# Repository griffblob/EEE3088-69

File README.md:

# EEE3088 Micromouse Project
## Group 69 
(Nice)
## Student Numbers:
TRCGRI001
SFRREN001

The project for our EEE3088F Electrcial Design course requires that we each design subsystems that will be integrated to build a Micro-mouse. This project covers the design and production of the sensing and power subsystems. Other systems such as processing subsystem, and motherboard are provided to us.

In this repository, one will find the detailed reports on how each subsystem was designed and tested and the gerber files for each subsystem.

Project files for the sensing subsystem can be found in: [Sensing](https://github.com/griffblob/EEE3088-69/tree/main/EEE3088%20Sensing)

Project files for the power subsystem can be found in: [Power](https://github.com/griffblob/EEE3088-69/tree/main/EEE3088%20Power)

Our reports can be found in [Reports](https://github.com/griffblob/EEE3088-69/tree/main/Reports). However, they will only be available after final submission closes to minimize the risk of plagarism.

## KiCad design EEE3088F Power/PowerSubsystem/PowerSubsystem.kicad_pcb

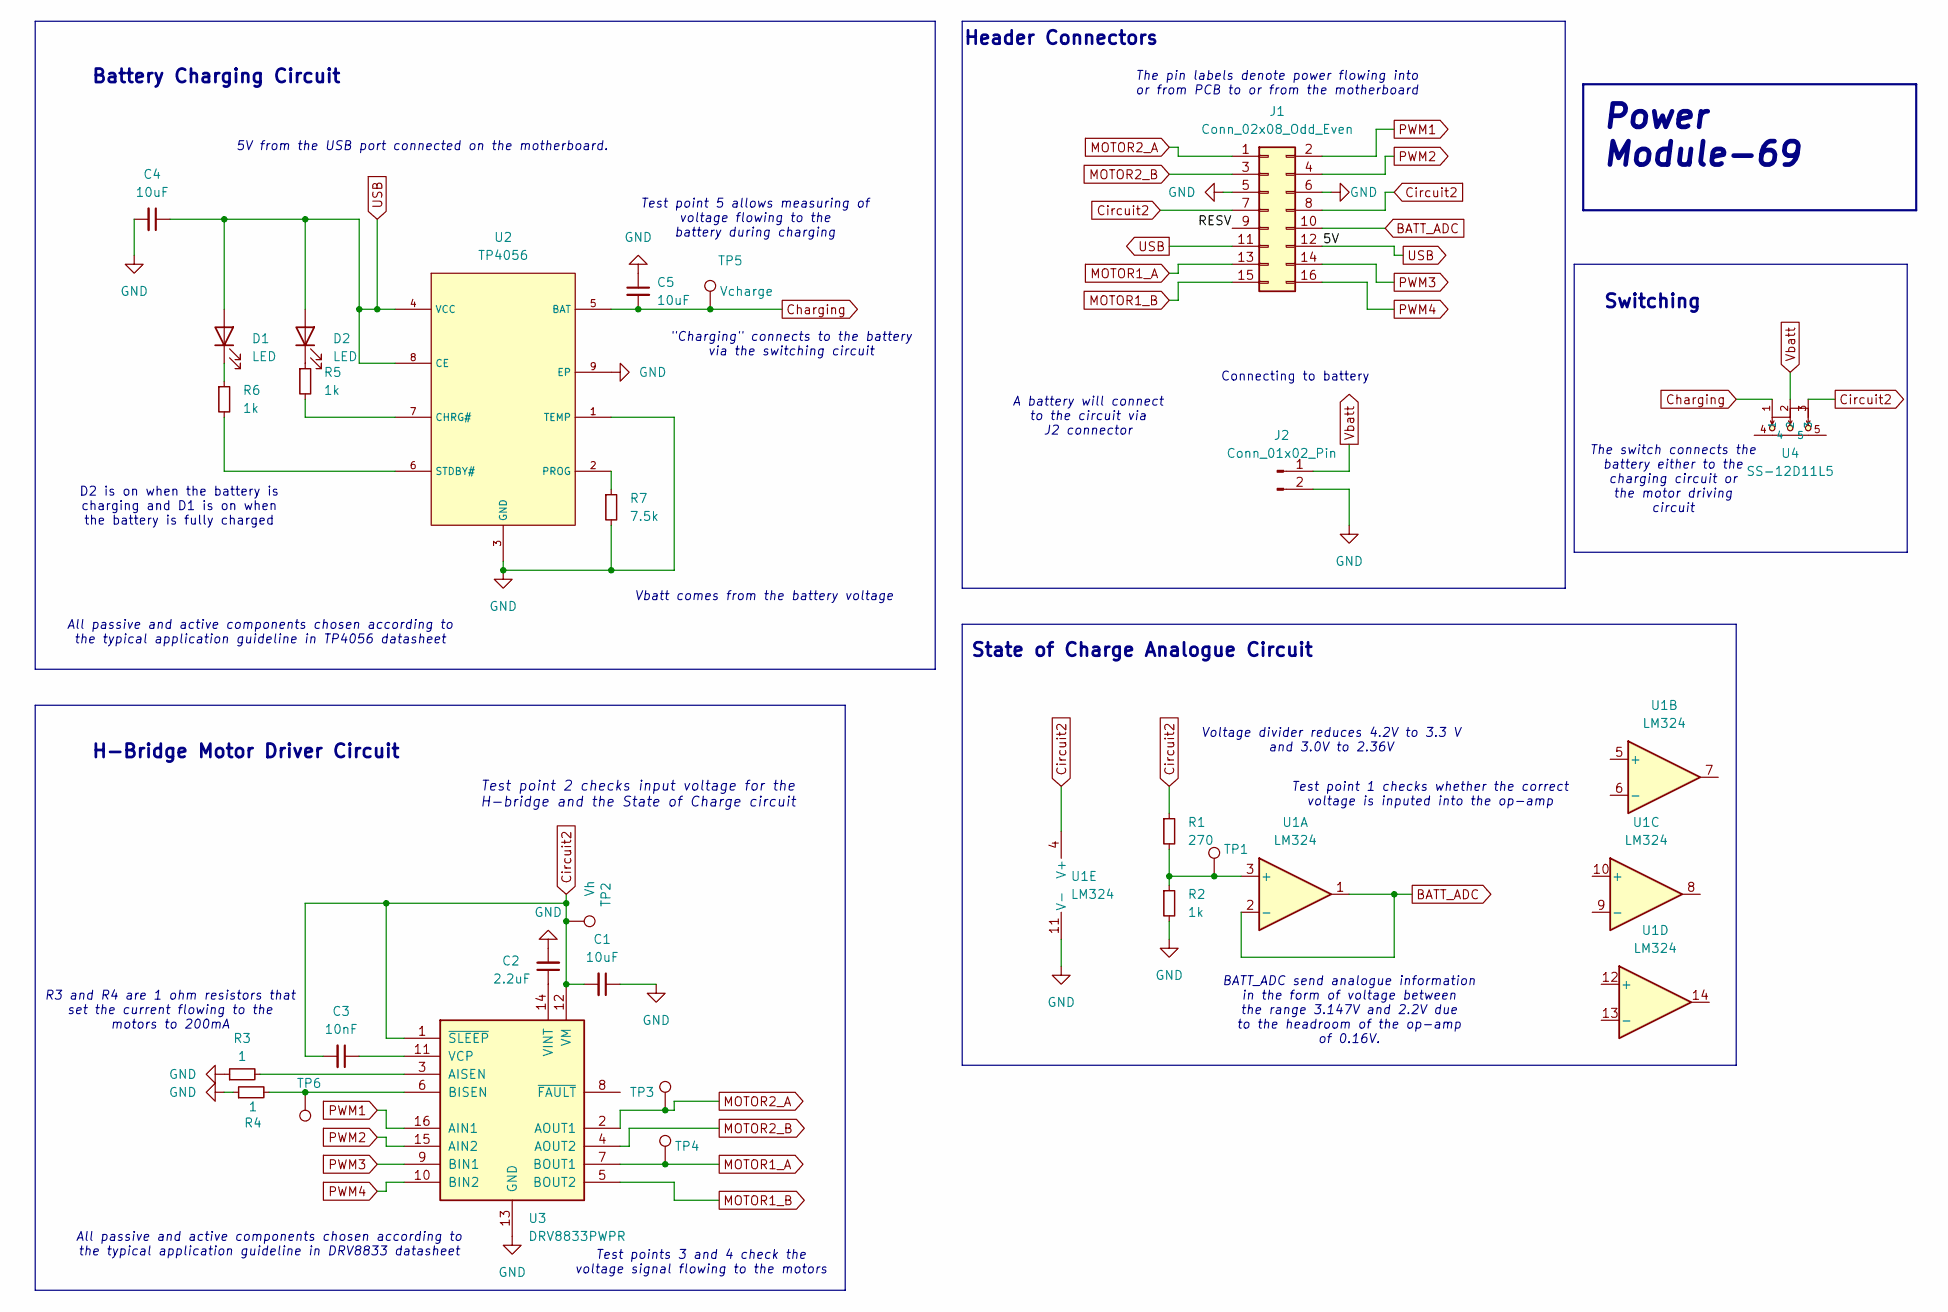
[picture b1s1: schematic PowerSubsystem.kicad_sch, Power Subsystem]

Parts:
C1, C4, C5: 10uF; C_0603_1608Metric; LCSC C19702
C2: 2.2uF; C_0603_1608Metric; LCSC C23630
C3: 10nF; C_0603_1608Metric; LCSC C57112
D1: LED; LED_0603_1608Metric; LCSC C2290
D2: LED; LED_0603_1608Metric; LCSC C2286
J1: Conn_02x08_Odd_Even; PinHeader_2x08_P2.54mm_Vertical
J2: Conn_01x02_Pin; JST_PH_B2B-PH-K_1x02_P2.00mm_Vertical
R1: 270; R_0603_1608Metric; LCSC C22966
R2, R5, R6: 1k; R_0603_1608Metric; LCSC C21190
R3, R4: 1; R_0603_1608Metric; LCSC C22936
R7: 7.5k; R_0603_1608Metric; LCSC C4211
TP1: Vadc; TestPoint_Pad_1.0x1.0mm
TP2: Vh; TestPoint_Pad_1.0x1.0mm
TP3: Vm1; TestPoint_Pad_1.0x1.0mm
TP4: Vm2; TestPoint_Pad_1.0x1.0mm
TP5: Vcharge; TestPoint_Pad_1.0x1.0mm
TP6: TestPoint; TestPoint_Pad_1.0x1.0mm
U1: LM324
U2: TP4056; ESOP-8_L4.9-W3.9-P1.27-LS6.0-BL-EP; LCSC C16581
U3: DRV8833PWPR; TSSOP-16-1EP_4.4x5mm_P0.65mm; LCSC C50506
U4: SS-12D11L5; SW-TH_SS-12D11L5; LCSC C319010

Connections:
/RESV: J1.9
BATT_ADC: J1.10, U1.1, U1.2 (-)
Charging: C5.2, TP5.1, U2.5 (BAT), U4.1
Circuit2: C1.2, C3.2, J1.7, J1.8, R1.1, TP2.1, U1.4 (V+), U3.1 (~SLEEP), U3.12 (VM), U4.3
GND: C1.1, C2.2, C4.2, C5.1, J1.5, J1.6, J2.2, R2.2, R3.1, R4.1, R7.2, U1.11 (V-), U2.1 (TEMP), U2.3 (GND), U2.9 (EP), U3.13 (GND), U3.17 (GND)
MOTOR1_A: J1.13, TP4.1, U3.7 (BOUT1)
MOTOR1_B: J1.15, U3.5 (BOUT2)
MOTOR2_A: J1.1, TP3.1, U3.2 (AOUT1)
MOTOR2_B: J1.3, U3.4 (AOUT2)
unnamed: D1.1 (K), R6.1
unnamed: D2.1 (K), R5.1
unnamed: R1.2, R2.1, TP1.1, U1.3 (+)
unnamed: R5.2, U2.7 (CHRG#)
unnamed: R7.1, U2.2 (PROG)
unnamed: R6.2, U2.6 (STDBY#)
unnamed: R3.2, U3.3 (AISEN)
unnamed: R4.2, TP6.1, U3.6 (BISEN)
unnamed: C3.1, U3.11 (VCP)
unnamed: C2.1, U3.14 (VINT)
PWM1: J1.2, U3.16 (AIN1)
PWM2: J1.4, U3.15 (AIN2)
PWM3: J1.14, U3.9 (BIN1)
PWM4: J1.16, U3.10 (BIN2)
USB: C4.1, D1.2 (A), D2.2 (A), J1.11, J1.12, U2.4 (VCC), U2.8 (CE)
Vbatt: J2.1, U4.2

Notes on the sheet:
Battery Charging Circuit
H-Bridge Motor Driver Circuit
Power Module-69
Switching
BATT_ADC send analogue information in the form of voltage between the range 3.147V and 2.2V due to the headroom of the op-amp of 0.16V.
Test point 1 checks whether the correct voltage is inputed into the op-amp
All passive and active components chosen according to the typical application guideline in DRV8833 datasheet
The switch connects the battery either to the charging circuit or the motor driving circuit
Test point 2 checks input voltage for the H-bridge and the State of Charge circuit
All passive and active components chosen according to the typical application guideline in TP4056 datasheet
Connecting to battery
5V from the USB port connected on the motherboard.
Test points 3 and 4 check the voltage signal flowing to the motors
Header Connectors
Voltage divider reduces 4.2V to 3.3 V and 3.0V to 2.36V
"Charging" connects to the battery via the switching circuit
A battery will connect to the circuit via J2 connector
D2 is on when the battery is charging and D1 is on when the battery is fully charged
R3 and R4 are 1 ohm resistors that set the current flowing to the motors to 200mA
Test point 5 allows measuring of voltage flowing to the battery during charging
State of Charge Analogue Circuit
Vbatt comes from the battery voltage
The pin labels denote power flowing into or from PCB to or from the motherboard

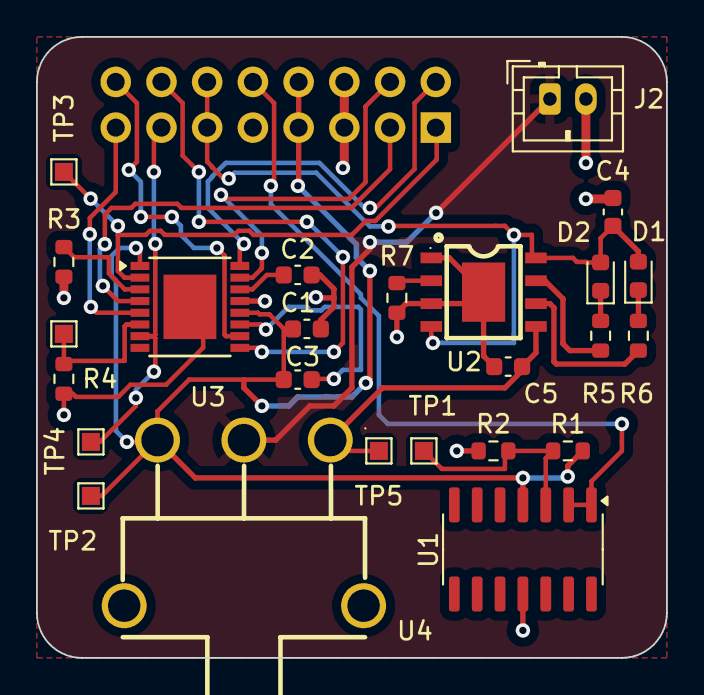
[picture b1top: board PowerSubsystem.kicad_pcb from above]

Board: 2 copper layers, 35.0 x 34.5 mm, 26 parts (1 on the bottom side), 24 nets.

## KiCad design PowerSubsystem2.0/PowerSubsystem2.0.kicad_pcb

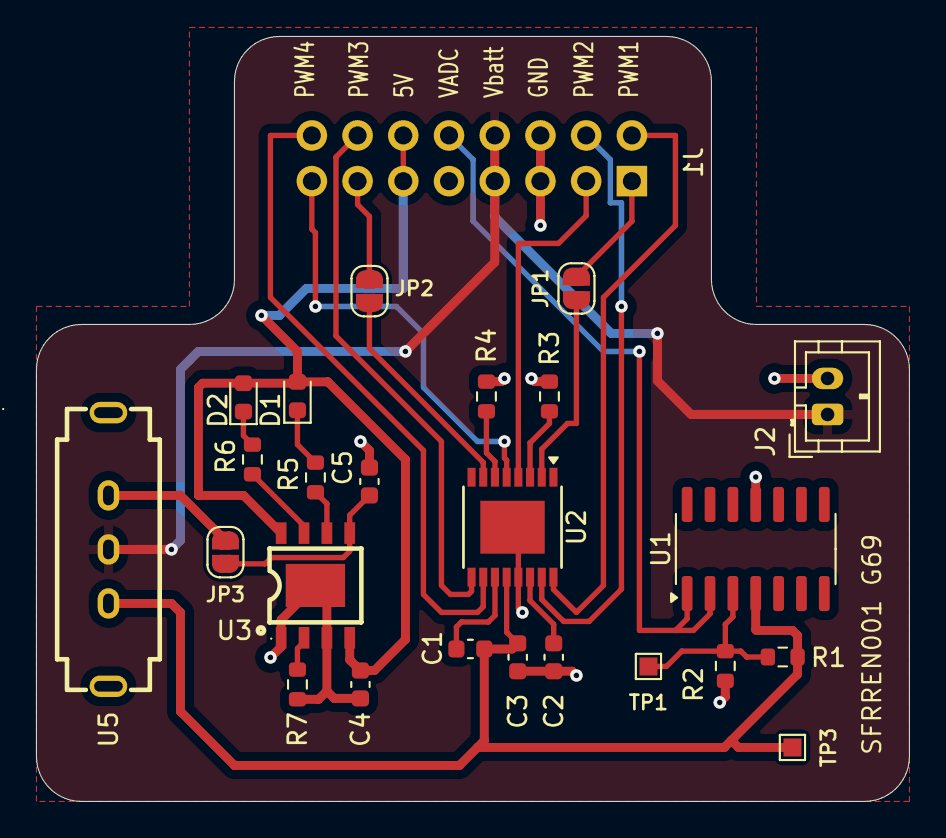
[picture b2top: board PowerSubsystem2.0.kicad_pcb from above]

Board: 2 copper layers, 48.5 x 42.5 mm, 25 parts (1 on the bottom side), 27 nets.

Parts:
C1: 10nF; C_0603_1608Metric
C2: 2.2uF; C_0603_1608Metric
C3, C4, C5: 10uF; C_0603_1608Metric
D1, D2: LED; LED_0603_1608Metric
J1: Conn_02x08_Odd_Even; PinHeader_2x08_P2.54mm_Vertical
J2: Conn_01x02_Pin; JST_PH_B2B-PH-K_1x02_P2.00mm_Vertical
JP1, JP2, JP3: SolderJumper_2_Open; SolderJumper-2_P1.3mm_Open_RoundedPad1.0x1.5mm
R1: 270; R_0603_1608Metric
R2, R5, R6: 1k; R_0603_1608Metric
R3, R4: 1; R_0603_1608Metric
R7: 7.5k; R_0603_1608Metric
TP1: Vadc; TestPoint_Pad_1.0x1.0mm
TP3: Vh; TestPoint_Pad_1.0x1.0mm
U1: LM324; SOIC-14_3.9x8.7mm_P1.27mm
U2: DRV8833PWPR; TSSOP-16-1EP_4.4x5mm_P0.65mm
U3: TP4056; ESOP-8_L4.9-W3.9-P1.27-LS6.0-BL-EP
U5: SK-12F02-G030; SW-TH_G-SWITCH_SK-12F02-G030

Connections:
/Motor1_A: J1.13, JP2.2 (B)
/Motor1_B: J1.15, U2.5 (BOUT2)
/Motor2_A: J1.1, JP1.2 (B)
/Motor2_B: J1.3, U2.4 (AOUT2)
/PWM1: J1.2, U2.16 (AIN1)
/PWM2: J1.4, U2.15 (AIN2)
/PWM3: J1.14, U2.9 (BIN1)
/PWM4: J1.16, U2.10 (BIN2)
/Vbatt: J1.7, J1.8, J2.1, U5.2
/Vusb: C4.1, D1.2 (A), D2.2 (A), J1.11, J1.12, U3.4 (VCC), U3.8 (CE)
Charging: JP3.2 (B), U5.1
GND: C2.2, C3.1, C4.2, C5.1, J1.5, J1.6, J2.2, R2.2, R3.1, R4.1, R7.2, U1.11 (V-), U2.13 (GND), U2.17 (GND), U3.1 (TEMP), U3.3 (GND), U3.9 (EP)
H-bridge: C1.2, C3.2, R1.1, TP3.1, U1.4 (V+), U2.12 (VM), U5.3
unnamed: D1.1 (K), R5.1
unnamed: D2.1 (K), R6.1
unnamed: JP1.1 (A), U2.2 (AOUT1)
unnamed: JP2.1 (A), U2.7 (BOUT1)
unnamed: C5.2, JP3.1 (A), U3.5 (BAT)
unnamed: R1.2, R2.1, TP1.1, U1.3 (+)
unnamed: R3.2, U2.3 (AISEN)
unnamed: R4.2, U2.6 (BISEN)
unnamed: C1.1, U2.11 (VCP)
unnamed: C2.1, U2.14 (VINT)
unnamed: R6.2, U3.7 (CHRG#)
unnamed: R7.1, U3.2 (PROG)
unnamed: R5.2, U3.6 (STDBY#)
VADC: J1.10, U1.1, U1.2 (-)

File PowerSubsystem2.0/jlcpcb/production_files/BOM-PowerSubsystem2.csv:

Comment,Designator,Footprint,LCSC
TP4056,U3,ESOP-8_L4.9-W3.9-P1.27-LS6.0-BL-EP,C16581
1k,"R2,R5,R6",R_0603_1608Metric,C21190
LED,D2,LED_0603_1608Metric,C2286
LED,D1,LED_0603_1608Metric,C2290
1,"R3,R4",R_0603_1608Metric,C22936
270,R1,R_0603_1608Metric,C22966
7.5k,R7,R_0603_1608Metric,C23234
2.2uF,C2,C_0603_1608Metric,C23630
SK-12F02-G030,U5,SW-TH_G-SWITCH_SK-12F02-G030,C2848892
DRV8833PWPR,U2,TSSOP-16-1EP_4.4x5mm_P0.65mm,C50506
10nF,C1,C_0603_1608Metric,C57112
LM324,U1,SOIC-14_3.9x8.7mm_P1.27mm,C71035
10uF,"C3,C4,C5",C_0603_1608Metric,C96446

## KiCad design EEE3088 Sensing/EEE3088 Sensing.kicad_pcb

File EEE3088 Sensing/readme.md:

# Sensing Subsystem
This subsystem was designed by TRCGRI001 and is they eyes of our robot

Here you will find the KICAD project files. 

🍑

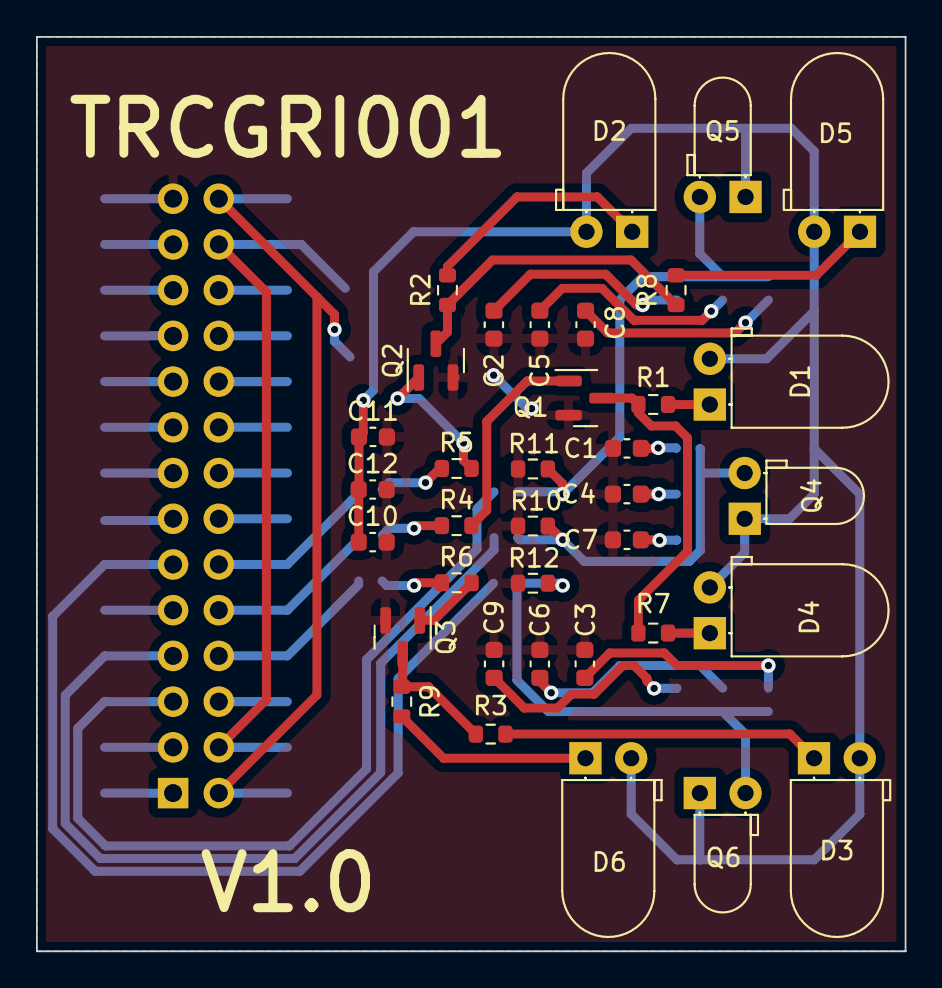
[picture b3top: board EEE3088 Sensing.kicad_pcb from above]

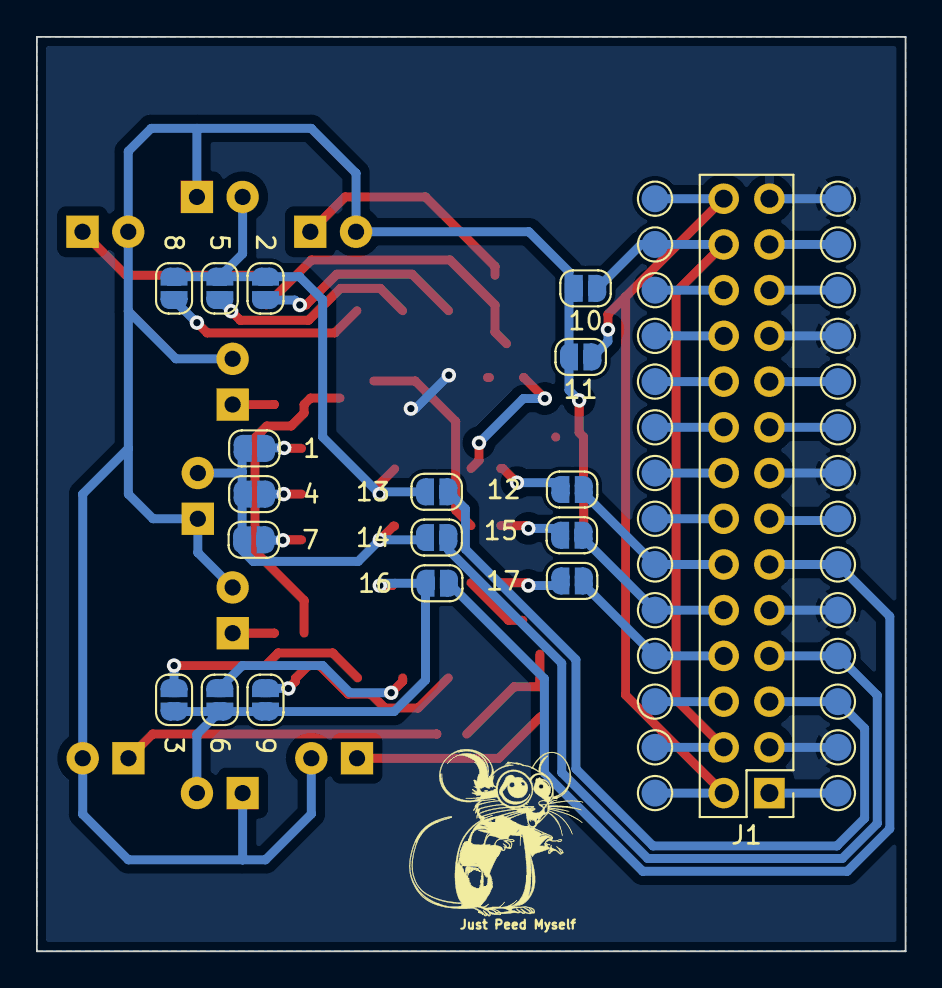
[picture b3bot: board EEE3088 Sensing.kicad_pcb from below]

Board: 2 copper layers, 48.3 x 50.8 mm, 82 parts (46 on the bottom side), 50 nets.

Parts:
1, 2, 3, 4, 5, 6, 7, 8, 9, 10, 11, 12, 13, 14, 15, 16, 17: SolderJumper_2_Open; SolderJumper-2_P1.3mm_Open_RoundedPad1.0x1.5mm
C1, C2, C3, C10: 100n CC0603KRX7R9BB104; C_0603_1608Metric
C4, C5, C6: 10n 0603B103K500NT; C_0603_1608Metric
C7, C8, C9: 1n CL10B102KB8NNNC; C_0603_1608Metric
C11: 2.2u CL10A225KO8NNNC; C_0603_1608Metric
C12: 10u CL10A106MA8NRNC; C_0603_1608Metric
D1, D2, D3, D4, D5, D6: SFH 4544; LED_D5.0mm_Horizontal_O1.27mm_Z3.0mm_IRBlack
J1: Conn_02x14_Odd_Even; PinHeader_2x14_P2.54mm_Vertical
Q1, Q2, Q3: BC847; SOT-23
Q4, Q5, Q6: TEFT4300; LED_D3.0mm_Horizontal_O1.27mm_Z2.0mm_IRBlack
R1, R2, R3, R7, R8, R9: 10; R_0603_1608Metric
R4, R5, R6: 620; R_0603_1608Metric
R10, R11, R12: 1.8K; R_0603_1608Metric
TP1, TP2, TP3, TP4, TP5, TP6, TP7, TP8, TP9, TP10, TP11, TP12, TP13, TP14, TP15, TP16, TP17, TP18, TP19, TP20, TP21, TP22, TP23, TP24, TP25, TP26, TP27, TP28: TestPoint; TestPoint_Pad_D1.5mm

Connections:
3V3: 11.1 (A), J1.2, J1.28, TP15.1, TP28.1
AB0: J1.25, TP13.1
BATT: 10.1 (A), J1.4, J1.26, TP16.1, TP27.1
GND: C1.2, C2.2, C3.2, C4.2, C5.2, C6.2, C7.2, C8.2, C9.2, C10.2, C11.2, C12.2, J1.3, J1.9, J1.15, J1.21, J1.27, Q1.2 (E), Q2.2 (E), Q3.2 (E), R10.2, R11.2, R12.2, TP2.1, TP5.1, TP8.1, TP11.1, TP14.1
unnamed: 1.1 (A), C1.1
unnamed: 2.1 (A), C2.1
unnamed: 3.1 (A), C3.1
unnamed: 4.1 (A), C4.1
unnamed: 5.1 (A), C5.1
unnamed: 6.1 (A), C6.1
unnamed: 7.1 (A), C7.1
unnamed: 8.1 (A), C8.1
unnamed: 9.1 (A), C9.1
unnamed: D1.1 (K), R1.1
unnamed: D2.1 (K), R2.1
unnamed: D3.1 (K), R3.1
unnamed: D4.1 (K), R7.1
unnamed: D5.1 (K), R8.1
unnamed: D6.1 (K), R9.1
unnamed: Q1.1 (B), R4.2
unnamed: Q1.3 (C), R1.2, R7.2
unnamed: Q2.1 (B), R5.2
unnamed: Q2.3 (C), R2.2, R8.2
unnamed: Q3.1 (B), R6.2
unnamed: Q3.3 (C), R3.2, R9.2
PA3: 13.1 (A), J1.5, TP3.1
PA4: 14.1 (A), J1.7, TP4.1
PA5: 16.1 (A), J1.11, TP6.1
PA6: J1.13, TP7.1
PA7: J1.17, TP9.1
PC4: J1.19, TP10.1
PC5: J1.23, TP12.1
PE8: J1.22, TP25.1
PE9: J1.20, TP24.1
PE10: J1.18, TP23.1
PE11: J1.16, TP22.1
PE12: J1.14, TP21.1
PE13: 12.1 (A), J1.12, TP20.1
PE14: 15.1 (A), J1.10, TP19.1
PE15: 17.1 (A), J1.8, TP18.1
RESV1: J1.24, TP26.1
RESV2: J1.6, TP17.1
RESV3: J1.1, TP1.1
VinL: 12.2 (B), R5.1
VinM: 15.2 (B), R4.1
VinR: 17.2 (B), R6.1
VoutL: 2.2 (B), 5.2 (B), 8.2 (B), 13.2 (B), Q5.2 (E), R11.1
VoutM: 1.2 (B), 4.2 (B), 7.2 (B), 14.2 (B), Q4.2 (E), R10.1
VoutR: 3.2 (B), 6.2 (B), 9.2 (B), 16.2 (B), Q6.2 (E), R12.1
vcc: 10.2 (B), 11.2 (B), C10.1, C11.1, C12.1, D1.2 (A), D2.2 (A), D3.2 (A), D4.2 (A), D5.2 (A), D6.2 (A), Q4.1 (C), Q5.1 (C), Q6.1 (C)

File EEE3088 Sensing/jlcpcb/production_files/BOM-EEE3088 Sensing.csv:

Comment,Designator,Footprint,LCSC
TEFT4300,"Q4,Q5,Q6",LED_D3.0mm_Horizontal_O1.27mm_Z2.0mm_IRBlack,C118301
100n CC0603KRX7R9BB104,"C1,C10,C2,C3",C_0603_1608Metric,C14663
1n CL10B102KB8NNNC,"C7,C8,C9",C_0603_1608Metric,C1588
10,"R1,R2,R3,R7,R8,R9",R_0603_1608Metric,C22859
620,"R4,R5,R6",R_0603_1608Metric,C23220
2.2u CL10A225KO8NNNC,C11,C_0603_1608Metric,C23630
 SFH 4544,"D1,D2,D3,D4,D5,D6",LED_D5.0mm_Horizontal_O1.27mm_Z3.0mm_IRBlack,C2900370
1.8K,"R10,R11,R12",R_0603_1608Metric,C4177
10n 0603B103K500NT,"C4,C5,C6",C_0603_1608Metric,C57112
BC847,"Q1,Q2,Q3",SOT-23,C7420337
10u CL10A106MA8NRNC,C12,C_0603_1608Metric,C96446

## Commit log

2024-04-21 Added Sensing Files
    Added KICAD Sensing Files
2024-04-21 Added Reports File
2024-04-22 Added power files.
